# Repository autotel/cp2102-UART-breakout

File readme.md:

Breakout board for CP2102 USB to UART bridge, to aid the design of boards using this chip.
This design hasn't been ever manufactured yet, but in theory you should be able to have it produced on any common aggregagor and have it working.

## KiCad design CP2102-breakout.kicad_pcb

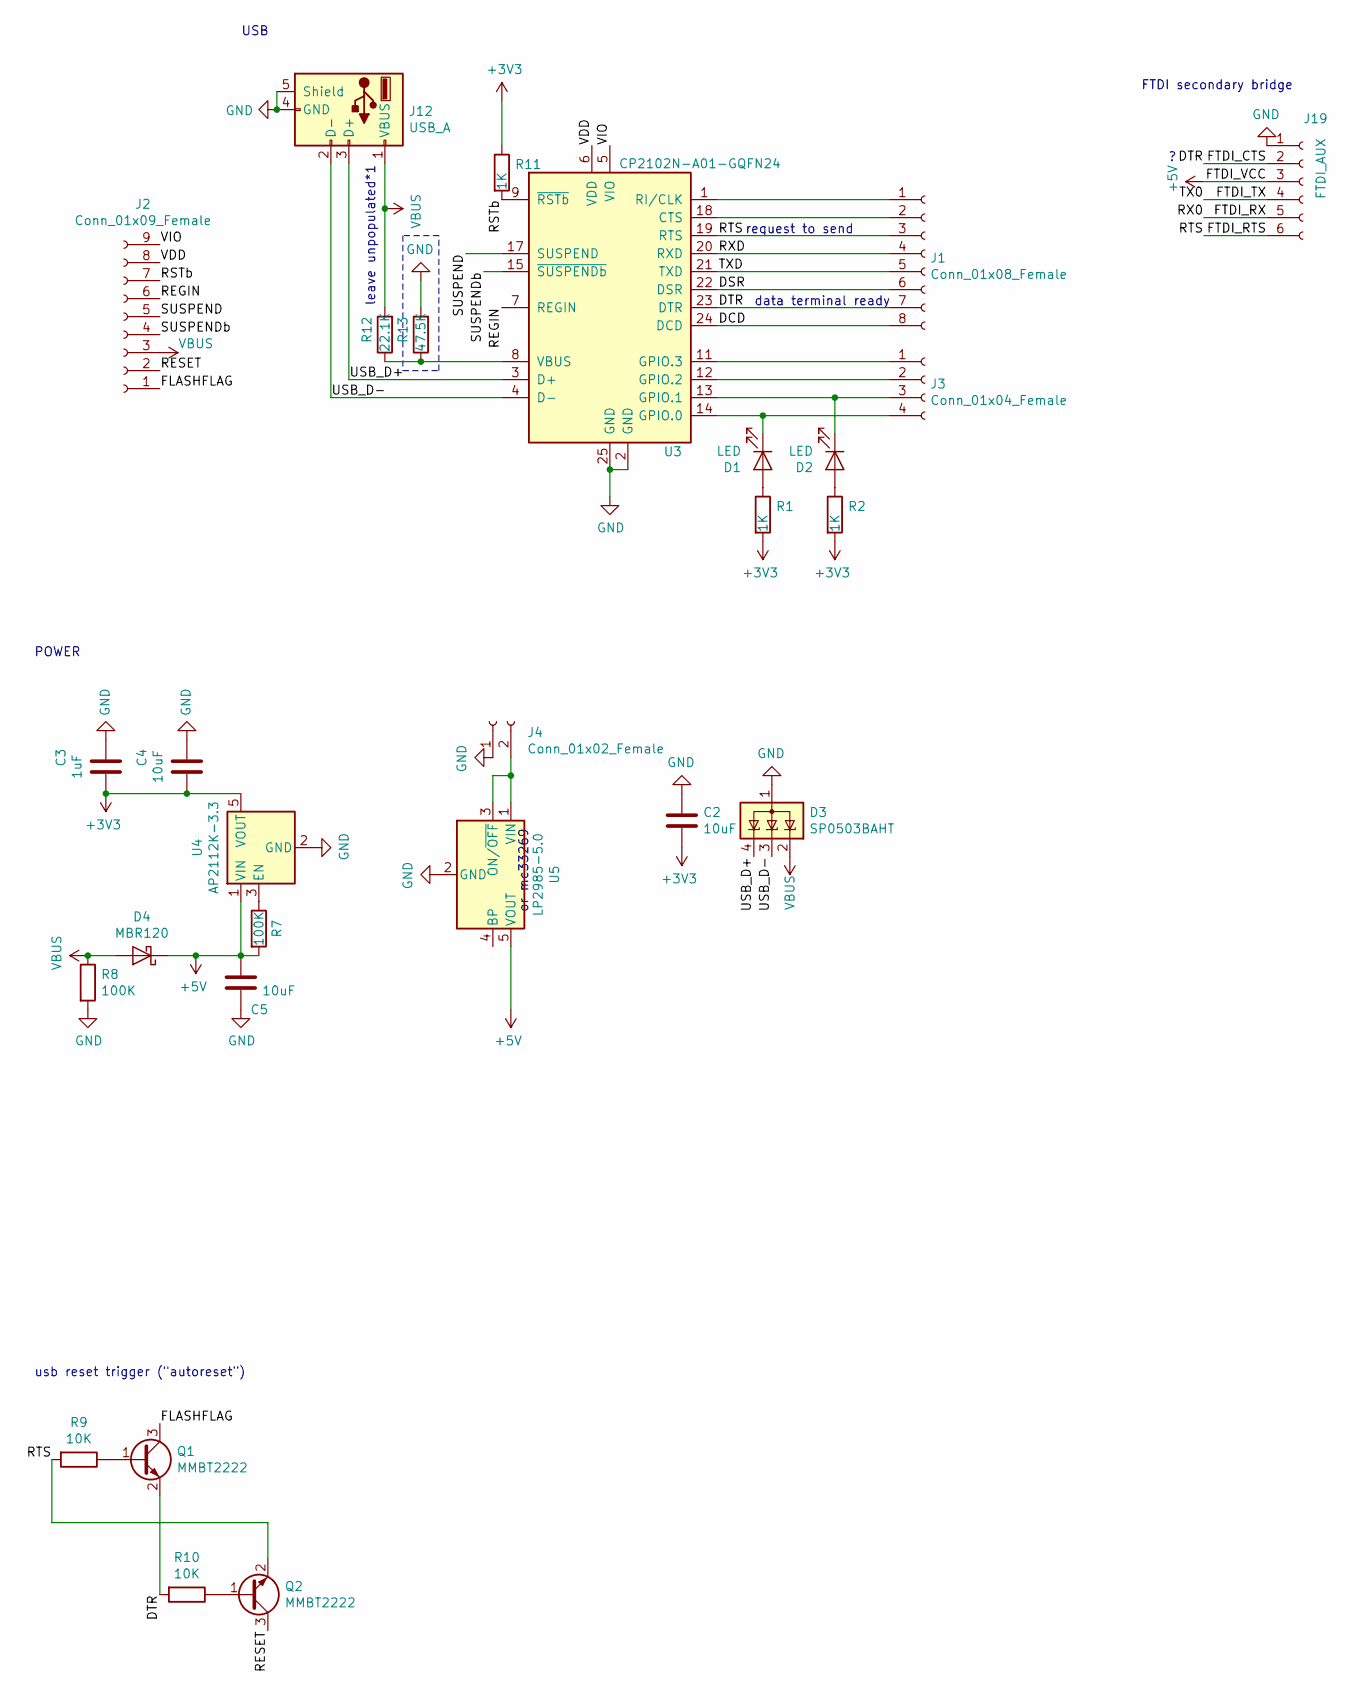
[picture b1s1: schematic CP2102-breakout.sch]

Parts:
C2, C4, C5: 10uF; C_0603_1608Metric_Pad1.05x0.95mm_HandSolder; MPN CL21A106KPFNNNE; LCSC PN C17024
C3: 1uF; C_0603_1608Metric_Pad1.05x0.95mm_HandSolder; MPN CL10A105KB8NNNC; LCSC PN C15849
D1, D2: LED; D_0603_1608Metric_Pad1.05x0.95mm_HandSolder; MPN 150060GS75000
D3: SP0503BAHT; SOT-143
D4: MBR120; D_SOD-123; MPN LMBR120FT1G; LCSC PN C81143
J1: Conn_01x08_Female; PinHeader_1x08_P2.54mm_Vertical
J2: Conn_01x09_Female; PinHeader_1x09_P2.54mm_Vertical
J3: Conn_01x04_Female; PinHeader_1x04_P2.54mm_Vertical
J4: Conn_01x02_Female; PinHeader_1x02_P2.54mm_Vertical
J12: USB_A; USB_B_OST_USB-B1HSxx_Horizontal; MPN --; LCSC PN --
J19: FTDI_AUX; PinHeader_1x06_P2.54mm_Vertical
Q1, Q2: MMBT2222; SOT-23; MPN MMBT2222ALT1G; LCSC PN C82460
R1, R2, R11: 1K; R_0603_1608Metric; MPN 0603WAJ0102T5E; LCSC PN C25585
R7, R8: 100K; R_0603_1608Metric; MPN 0603WAF1003T5E; LCSC PN C25803
R9, R10: 10K; R_0603_1608Metric; MPN RC0603FR-0710KL; LCSC PN C98220
R12: 22.1K; R_Axial_DIN0204_L3.6mm_D1.6mm_P7.62mm_Horizontal; MPN --; LCSC PN --
R13: 47.5K; R_Axial_DIN0204_L3.6mm_D1.6mm_P7.62mm_Horizontal; MPN --; LCSC PN --
U3: CP2102N-A01-GQFN24; QFN-28-1EP_5x5mm_P0.5mm_EP3.35x3.35mm; MPN CP2102-GMR; LCSC PN C6568
U4: AP2112K-3.3; TSOT-23-5; MPN AP2112K-3.3TRG1; LCSC PN C51118
U5: LP2985-5.0; TSOT-23-5; MPN LP2985AIM5X-5.0/NOPB; LCSC PN C311788

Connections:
+3V3: C2.2, C3.2, C4.2, R1.2, R2.2, R11.1, U4.5 (VOUT)
+5V: C5.1, D4.1 (K), J19.3, R7.2, U4.1 (VIN), U5.5 (VOUT)
/DCD: J1.8, U3.24 (DCD)
/DSR: J1.6, U3.22 (DSR)
/DTR: J1.7, J19.2, Q1.2 (E), R10.2, U3.23 (DTR)
/FLASHFLAG: J2.1, Q1.3 (C)
/FTDI_RTS: J1.3, J19.6, Q2.2 (E), R9.2, U3.19 (RTS)
/FTDI_RX: J19.5
/FTDI_TX: J19.4
/REGIN: J2.6, U3.7 (REGIN)
/RESET: J2.2, Q2.3 (C)
/RSTb: J2.7, R11.2, U3.9 (~RSTb)
/RXD: J1.4, U3.20 (RXD)
/SUSPEND: J2.5, U3.17 (SUSPEND)
/SUSPENDb: J2.4, U3.15 (~SUSPENDb)
/TXD: J1.5, U3.21 (TXD)
/USB_D+: D3.4 (K), J12.3 (D+), U3.3 (D+)
/USB_D-: D3.3 (K), J12.2 (D-), U3.4 (D-)
/VDD: J2.8, U3.6 (VDD)
/VIO: J2.9, U3.5 (VIO)
GND: C2.1, C3.1, C4.1, C5.2, D3.1 (A), J4.1, J12.4 (GND), J12.5 (Shield), J19.1, R8.2, R13.2, U3.2 (GND), U3.25 (GND), U4.2 (GND), U5.2 (GND)
unnamed: D1.1 (K), J3.4, U3.14 (GPIO.0)
unnamed: D1.2 (A), R1.1
unnamed: D2.1 (K), J3.3, U3.13 (GPIO.1)
unnamed: D2.2 (A), R2.1
unnamed: J1.1, U3.1 (RI/CLK)
unnamed: J1.2, U3.18 (CTS)
unnamed: J3.1, U3.11 (GPIO.3)
unnamed: J3.2, U3.12 (GPIO.2)
unnamed: J4.2, U5.1 (VIN), U5.3 (ON/~OFF~)
unnamed: Q1.1 (B), R9.1
unnamed: Q2.1 (B), R10.1
unnamed: R7.1, U4.3 (EN)
unnamed: R12.1, R13.1, U3.8 (VBUS)
VBUS: D3.2 (K), D4.2 (A), J2.3, J12.1 (VBUS), R8.1, R12.2

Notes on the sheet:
usb reset trigger ("autoreset")
POWER
or mc33269
USB
leave unpopulated*1
FTDI secondary bridge
data terminal ready
request to send

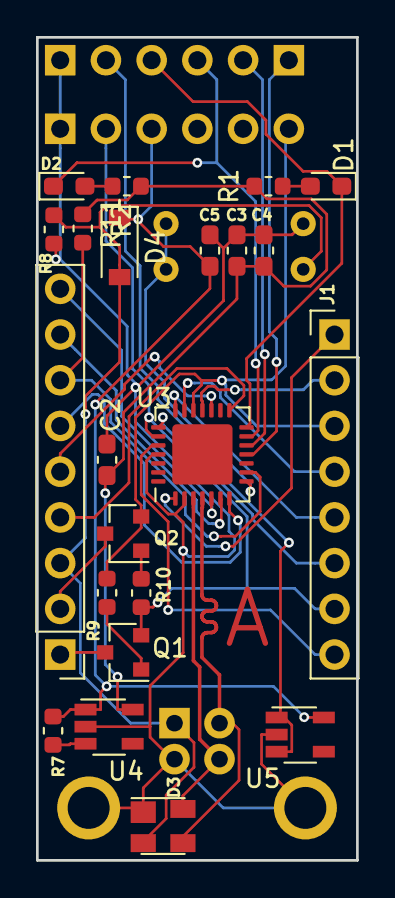
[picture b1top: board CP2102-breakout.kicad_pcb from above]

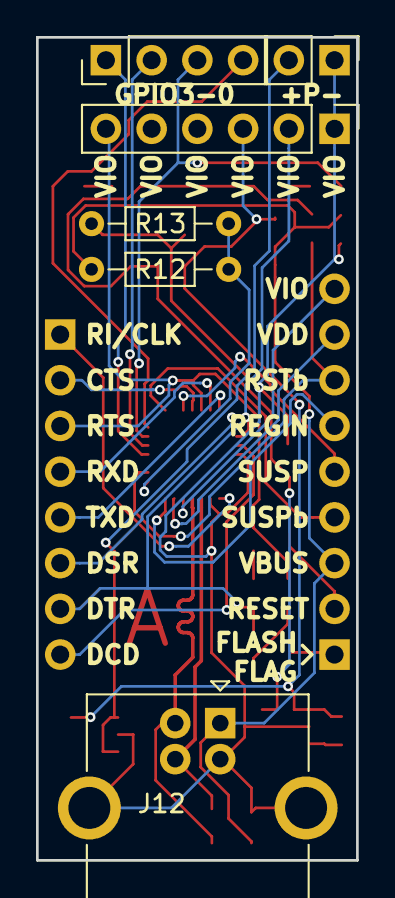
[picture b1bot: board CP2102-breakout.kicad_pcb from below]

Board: 2 copper layers, 17.8 x 45.7 mm, 28 parts (6 on the bottom side), 33 nets.

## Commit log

2019-09-12 ready
